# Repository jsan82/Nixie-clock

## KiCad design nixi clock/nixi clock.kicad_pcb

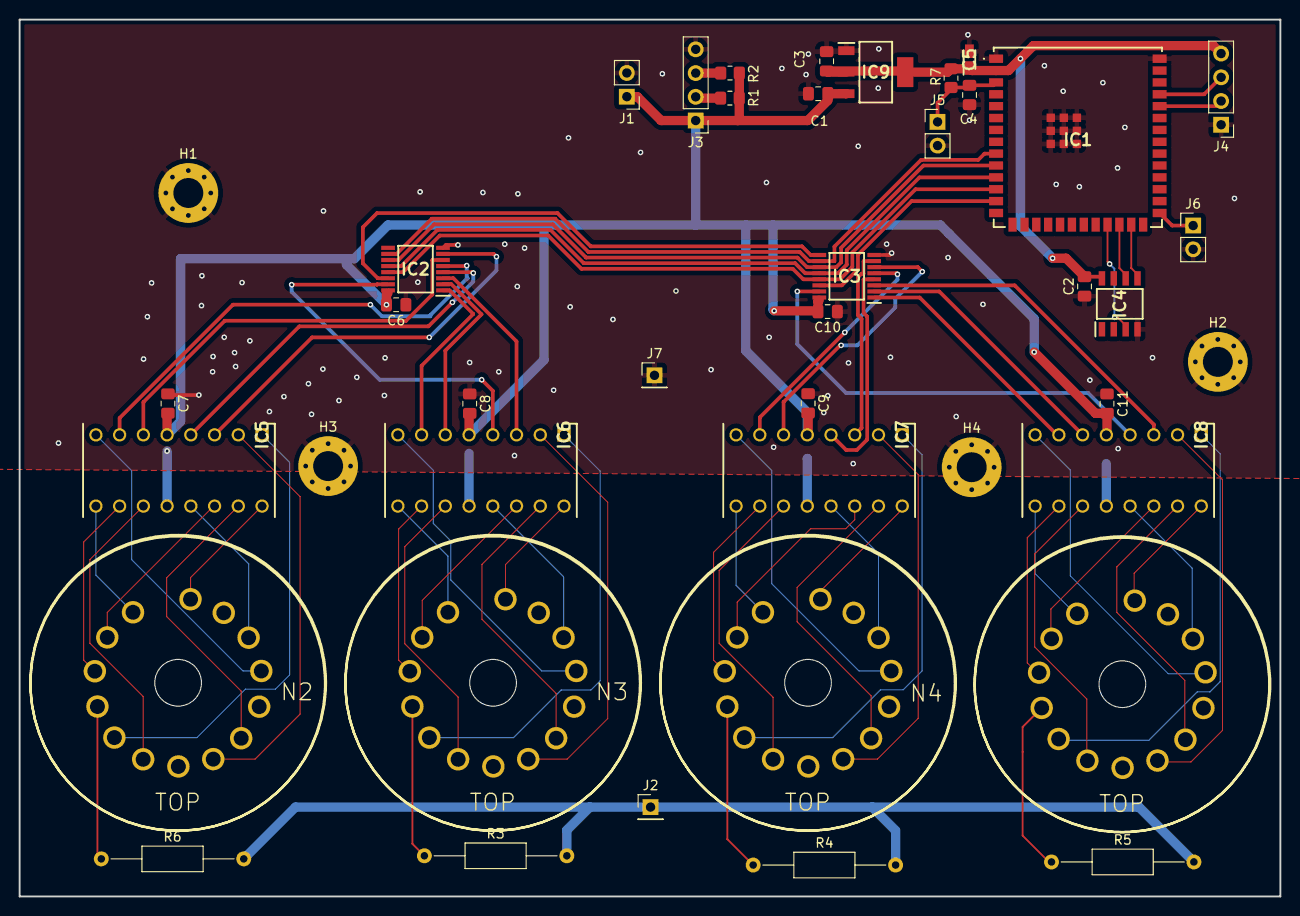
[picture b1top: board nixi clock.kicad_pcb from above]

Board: 2 copper layers, 134.9 x 93.8 mm, 42 parts (0 on the bottom side), 79 nets.

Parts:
C1, C2, C3, C4, C6, C7, C8, C9, C10, C11: 10u; C_0805_2012Metric_Pad1.18x1.45mm_HandSolder
C5: TMCP0G476MTR2F; CAPPM2012X120N
H1, H2, H3, H4: MountingHole_Pad; MountingHole_3.2mm_M3_Pad_Via
IC1: ESP32-S3-WROOM-1U-N4; ESP32S3WROOM1UN4
IC2, IC3: 74AHCT595PW-Q100,1; SOP65P640X110-16N
IC4: PCF85063AT_AY; SOIC127P600X175-8N
IC5, IC6, IC7, IC8: 74141; DIPS762W70P254L2032H510Q16N
IC9: LM1117MP-3.3_NOPB; SOT230P700X180-4N
J1, J5, J6: Conn_01x02; PinHeader_1x02_P2.54mm_Vertical
J2, J7: Conn_01x01; PinHeader_1x01_P2.54mm_Vertical
J3, J4: Conn_01x04; PinHeader_1x04_P2.54mm_Vertical
N1, N2, N3, N4: nixies-us-IN-4-DSUB
R1, R2: 4k7; R_0805_2012Metric_Pad1.20x1.40mm_HandSolder
R3, R4, R5, R6: 6k8; R_Axial_DIN0207_L6.3mm_D2.5mm_P15.24mm_Horizontal
R7: 10k; R_0805_2012Metric_Pad1.20x1.40mm_HandSolder

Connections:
+3.3V: C2.2, C3.2, C5.1 (+), IC1.2 (3V3), IC4.8 (VDD), IC9.2 (OUTPUT), IC9.4 (VOUT), J4.4, R7.1
+5V: C1.2, C6.2, C7.2, C8.2, C9.2, C10.2, C11.2, IC2.16 (VCC), IC3.16 (VCC), IC5.5, IC6.5, IC7.5, IC8.5, IC9.3 (INPUT), J1.1, J3.1, R1.1, R2.1
BOOT: IC1.27 (IO0), J6.1
D_CLK: IC1.10 (IO17), IC2.11 (SHCP), IC3.11 (SHCP)
EN: C4.1, IC1.3 (EN), J5.1, R7.2
GND: C1.1, C2.1, C3.1, C4.2, C5.2 (-), C6.1, C7.1, C8.1, C9.1, C10.1, C11.1, H1.1, H2.1, H3.1, H4.1, IC1.1 (GND_1), IC1.40 (GND_2), IC1.41 (GND_3), IC1.42 (GND_4), IC1.43 (GND_5), IC1.44 (GND_6), IC1.45 (GND_7), IC1.46 (GND_8), IC1.47 (GND_9), IC1.48 (GND_10), IC1.49 (GND_11), IC2.8 (GND), IC3.8 (GND), IC4.4 (VSS), IC5.12, IC6.12, IC7.12, IC8.12, IC9.1 (ADJ/GND), J1.2, J3.4, J4.1, J5.2, J6.2, J7.1
INT: IC1.23 (IO21), IC4.3 (~INT)
N1A: IC2.7 (Q7), IC5.3
N1B: IC2.6 (Q6), IC5.6
N1C: IC2.5 (Q5), IC5.7
N1D: IC2.4 (Q4), IC5.4
N2A: IC2.3 (Q3), IC6.3
N2B: IC2.2 (Q2), IC6.6
N2C: IC2.1 (Q1), IC6.7
N2D: IC2.15 (Q0), IC6.4
N3A: IC3.7 (Q7), IC7.3
N3B: IC3.6 (Q6), IC7.6
N3C: IC3.5 (Q5), IC7.7
N3D: IC3.4 (Q4), IC7.4
N4A: IC3.3 (Q3), IC8.3
N4B: IC3.2 (Q2), IC8.6
N4C: IC3.1 (Q1), IC8.7
N4D: IC3.15 (Q0), IC8.4
N10: IC5.2, N1.0
N11: IC5.16, N1.1
N12: IC5.15, N1.2
N13: IC5.8, N1.3
N14: IC5.9, N1.4
N15: IC5.13, N1.5
N16: IC5.14, N1.6
N17: IC5.11, N1.7
N18: IC5.10, N1.8
N19: IC5.1, N1.9
N20: IC6.2, N2.0
N21: IC6.16, N2.1
N22: IC6.15, N2.2
N23: IC6.8, N2.3
N24: IC6.9, N2.4
N25: IC6.13, N2.5
N26: IC6.14, N2.6
N27: IC6.11, N2.7
N28: IC6.10, N2.8
N29: IC6.1, N2.9
N30: IC7.2, N3.0
N31: IC7.16, N3.1
N32: IC7.15, N3.2
N33: IC7.8, N3.3
N34: IC7.9, N3.4
N35: IC7.13, N3.5
N36: IC7.14, N3.6
N37: IC7.11, N3.7
N38: IC7.10, N3.8
N39: IC7.1, N3.9
N40: IC8.2, N4.0
N41: IC8.16, N4.1
N42: IC8.15, N4.2
N43: IC8.8, N4.3
N44: IC8.9, N4.4
N45: IC8.13, N4.5
N46: IC8.14, N4.6
N47: IC8.11, N4.7
N48: IC8.10, N4.8
N49: IC8.1, N4.9
NIXI_DATA: IC1.13 (IO19), IC3.14 (DS)
NIXI_EN: IC1.12 (IO8), IC2.13 (~OE), IC3.13 (~OE)
unnamed: J3.2, R1.2
unnamed: J3.3, R2.2
unnamed: N1.A3 (A), R6.1
unnamed: N2.A3 (A), R3.1
unnamed: N3.A3 (A), R4.1
unnamed: N4.A3 (A), R5.1
O_CLK: IC1.11 (IO18), IC2.12 (STCP), IC3.12 (STCP)
R1DO: IC2.14 (DS), IC3.9 (Q7S)
RST: IC1.9 (IO16), IC2.10 (~MR), IC3.10 (~MR)
RXD: IC1.36 (RXD0), J4.2
SCL: IC1.24 (IO47), IC4.6 (SCL)
SDA: IC1.25 (IO48), IC4.5 (SDA)
TXD: IC1.37 (TXD0), J4.3
VBUS: J2.1, R3.2, R4.2, R5.2, R6.2

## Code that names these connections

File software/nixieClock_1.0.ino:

#include <WiFi.h>
#include "time.h"
#include "esp_sntp.h"


uint8_t rst = 16;
uint8_t d_clk = 17;
uint8_t o_clk = 18;
uint8_t nixi_en = 8;
uint8_t nixi_data = 19;
uint8_t rtc_int = 21;
uint8_t rtc_scl = 47;
uint8_t rtc_sda = 48;
uint8_t currentHour;
uint8_t currentMin;

const char *ssid = "HotPot";
const char *password = "ooYie3Ka";

const char *ntpServer1 = "pool.ntp.org";
const char *ntpServer2 = "time.nist.gov";
const long gmtOffset_sec = 3600;
const int daylightOffset_sec = 3600;

const char *time_zone = "CET-1CEST,M3.5.0,M10.5.0/3";  // TimeZone rule for Europe/Rome including daylight adjustment rules (optional)

void printLocalTime() {
  struct tm timeinfo;
  if (!getLocalTime(&timeinfo)) {
    Serial.println("No time available (yet)");
    return;
  }
  Serial.println(&timeinfo, "%A, %B %d %Y %H:%M:%S");
   
  int hour = timeinfo.tm_hour;
  int min = timeinfo.tm_min;
  
  if(currentHour != hour  || currentMin != min)
  {
    sendNumber(min%10);
    sendNumber(min/10);
    sendNumber(hour%10);
    sendNumber(hour/10);
    currentHour = timeinfo.tm_hour;
    currentMin = timeinfo.tm_min;
    Serial.println("new local time");
  } else {
    Serial.println("still same time");
  }

}

// Callback function (gets called when time adjusts via NTP)
void timeavailable(struct timeval *t) {
  Serial.println("Got time adjustment from NTP!");
  printLocalTime();
}

void sendToRegister(uint8_t bit)
{
  if (bit == 1)
  {
    digitalWrite(nixi_data, 1);
  } else {
    digitalWrite(nixi_data, 0);
  }

  delay(1);
  digitalWrite(d_clk, 1);
  delay(1);
  digitalWrite(o_clk,1);
  delay(1);
  digitalWrite(d_clk,0);
  delay(1);
  digitalWrite(o_clk,0);
  delay(1);
}

void sendNumber(uint8_t number)
{
  switch(number)
  {
    case 0:
      digitalWrite(nixi_en, 1);
      sendToRegister(1);
      sendToRegister(0);
      sendToRegister(0);
      sendToRegister(1);
      digitalWrite(nixi_en, 0);
      Serial.println("printing 0");
      break;
    case 1:
      digitalWrite(nixi_en, 1);
      sendToRegister(0);
      sendToRegister(0);
      sendToRegister(0);
      sendToRegister(0);
      digitalWrite(nixi_en, 0);
      Serial.println("printing 1");
      
      break;
    case 2:
      digitalWrite(nixi_en, 1);
      sendToRegister(1);
      sendToRegister(0);
      sendToRegister(0);
      sendToRegister(0);
      digitalWrite(nixi_en, 0);
      Serial.println("printing 2");
      break;
    case 3:
      digitalWrite(nixi_en, 1);
      sendToRegister(0);
      sendToRegister(1);
      sendToRegister(0);
      sendToRegister(0);
      digitalWrite(nixi_en, 0);
      Serial.println("printing 3");
      break;
    case 4:
      digitalWrite(nixi_en, 1);
      sendToRegister(1);
      sendToRegister(1);
      sendToRegister(0);
      sendToRegister(0);
      digitalWrite(nixi_en, 0);
      Serial.println("printing 4");
      break;
    case 5:
      digitalWrite(nixi_en, 1);
      sendToRegister(0);
      sendToRegister(0);
      sendToRegister(1);
      sendToRegister(0);
      digitalWrite(nixi_en, 0);
      Serial.println("printing 5");
      break;
    case 6:
      digitalWrite(nixi_en, 1);
      sendToRegister(1);
      sendToRegister(0);
      sendToRegister(1);
      sendToRegister(0);
      digitalWrite(nixi_en, 0);
      Serial.println("printing 6");
      break;
    case 7:
      digitalWrite(nixi_en, 1);
      sendToRegister(0);
      sendToRegister(1);
      sendToRegister(1);
      sendToRegister(0);
      digitalWrite(nixi_en, 0);
      Serial.println("printing 7");
      break;
    case 8:
      digitalWrite(nixi_en, 1);
      sendToRegister(1);
      sendToRegister(1);
      sendToRegister(1);
      sendToRegister(0);
      digitalWrite(nixi_en, 0);
      Serial.println("printing 8");
      break;
    case 9:
      digitalWrite(nixi_en, 1);
      sendToRegister(0);
      sendToRegister(0);
      sendToRegister(0);
      sendToRegister(1);
      digitalWrite(nixi_en, 0);
      Serial.println("printing 9");
      break;           
  }
}

void setup() {
  Serial.begin(115200);
  Serial.println("Starting");
  pinMode(rst, OUTPUT);
  pinMode(d_clk, OUTPUT);
  pinMode(o_clk, OUTPUT);
  pinMode(nixi_en, OUTPUT);
  pinMode(nixi_data, OUTPUT);
  digitalWrite(rst,1);
  digitalWrite(nixi_en, 0);

  struct tm timeinfo;
  currentHour = timeinfo.tm_hour;
  currentMin = timeinfo.tm_min;

  // First step is to configure WiFi STA and connect in order to get the current time and date.
  Serial.printf("Connecting to %s ", ssid);
  WiFi.begin(ssid, password);

  /**
   * NTP server address could be acquired via DHCP,
   *
   * NOTE: This call should be made BEFORE esp32 acquires IP address via DHCP,
   * otherwise SNTP option 42 would be rejected by default.
   * NOTE: configTime() function call if made AFTER DHCP-client run
   * will OVERRIDE acquired NTP server address
   */
  esp_sntp_servermode_dhcp(1);  // (optional)

  while (WiFi.status() != WL_CONNECTED) {
    delay(500);
    Serial.print(".");
  }
  Serial.println(" CONNECTED");

  // set notification call-back function
  sntp_set_time_sync_notification_cb(timeavailable);

  /**
   * This will set configured ntp servers and constant TimeZone/daylightOffset
   * should be OK if your time zone does not need to adjust daylightOffset twice a year,
   * in such a case time adjustment won't be handled automagically.
   */
  configTime(gmtOffset_sec, daylightOffset_sec, ntpServer1, ntpServer2);

  /**
   * A more convenient approach to handle TimeZones with daylightOffset
   * would be to specify a environment variable with TimeZone definition including daylight adjustmnet rules.
   * A list of rules for your zone could be obtained from https://github.com/esp8266/Arduino/blob/master/cores/esp8266/TZ.h
   */
  //configTzTime(time_zone, ntpServer1, ntpServer2);
}

void loop() {
  delay(5000);
  printLocalTime();
  // for(int i = 0; i <= 9; i++)
  // {
  //   digitalWrite(rst,0);
  //   digitalWrite(rst,1);
  //   sendNumber(i);
  //   sendNumber(i);
  //   sendNumber(i);
  //   sendNumber(i);
  //   delay(10000);
  // }

}

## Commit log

2024-10-15 decoder and more
2024-11-09 nixi clock
    first pcb version
2024-12-18 ESP32soft
    Program that connect to the internet and send hour to the nixie clock after some decoding because I messed up in kiCad and connect pins incorrectly
2024-12-24 Soft in version 0.9
    Almost done final for version 1.0
    Still need a little bit of clarity in code
2024-12-25 Version 1.0 of the software
    addet showing of the date if every 5 minute
2024-12-27 final 1.0
2025-01-29 renaming
